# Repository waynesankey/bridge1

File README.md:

This is a PCB design for a UART to WiFi bridge that goes with the bridge1_sw repo software.

The bridge has a Raspberry Pi Pico 2W microcontroller and runs AI generated MicroPython code.

The bridge is used to provide a web browser interface to remotely control a preamp.  The UART
connects to a microcontroller in the preamp that controls the local display, inputection relays,
mute relay, volume control chips, etc.

The bridge is housed in an inexpensive plastic box that need not be visible to the user and
is connected to the preamp by a 4-pin M12 A-coded umbilical cable.  The cable has female ends, while the
bridge and preamp both have 4-pin M12 A-coded male ends.

The signal chain is:

iPhone <-> WiFi <-> BRIDGE1 (Raspberry Pi Pico 2W) <-> UART (4-pin M12 cable) <-> Preamp (Raspberry Pi Pico)

And the iPhone controls and GUI show the state of the Preamp which holds the true state of the
system - so eg. if the volume decoder on the Preamp is used to adjust the volume, that change is
immediately seen on the iPhone GUI.

W. Sankey
2/9/26

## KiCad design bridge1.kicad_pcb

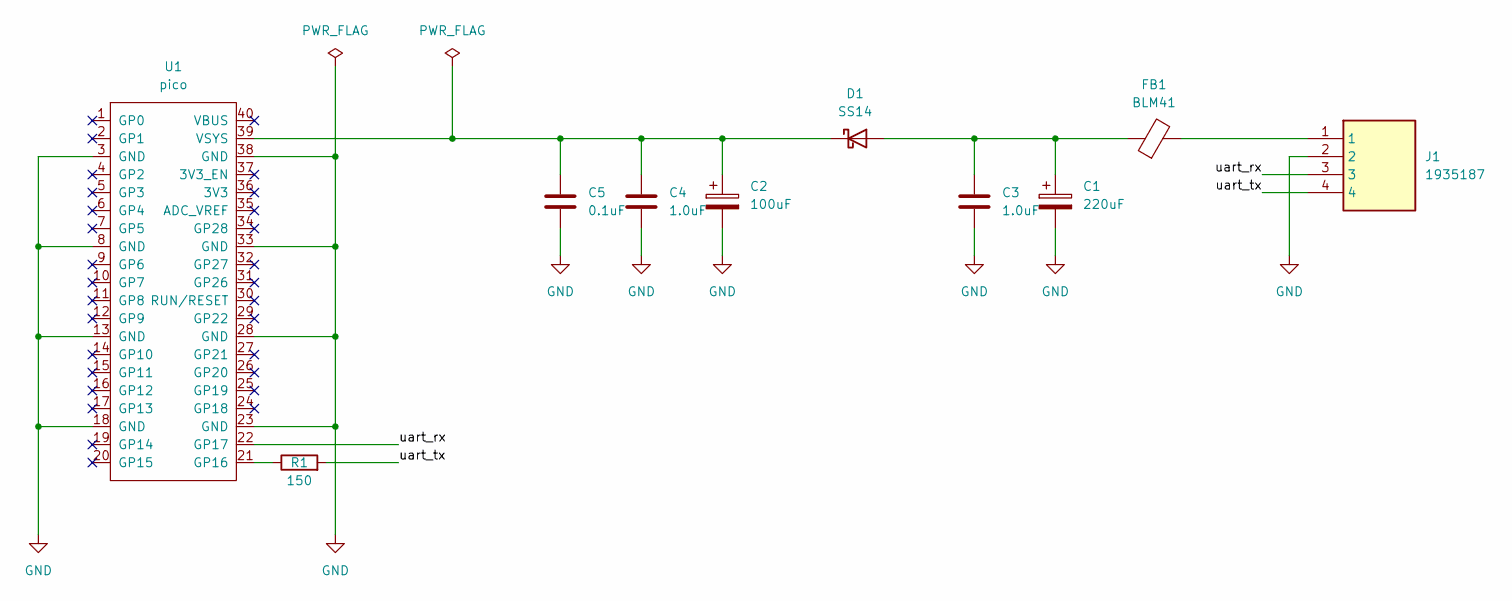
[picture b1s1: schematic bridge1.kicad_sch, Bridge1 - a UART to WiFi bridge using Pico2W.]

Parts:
C1: 220uF; EEE1AA221P
C2: 100uF; 16SVF180M
C3, C4: 1.0uF; C_1206_3216Metric
C5: 0.1uF; C_1206_3216Metric
D1: SS14; D_SMA
FB1: BLM41; L_1806_4516Metric
J1: 1935187; Mouser Part Number 651-1935187
R1: 150; R_0603_1608Metric
U1: pico; RaspberryPi_Pico_Common_Unspecified

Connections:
/uart_rx: J1.3, U1.22 (GP17)
/uart_tx: J1.4, R1.2
GND: C1.2, C2.2, C3.2, C4.2, C5.2, J1.2, U1.3 (GND), U1.8 (GND), U1.13 (GND), U1.18 (GND), U1.23 (GND), U1.28 (GND), U1.33 (GND), U1.38 (GND)
unnamed: C1.1, C3.1, D1.2 (A), FB1.1
unnamed: C2.1, C4.1, C5.1, D1.1 (K), U1.39 (VSYS)
unnamed: FB1.2, J1.1
unnamed: R1.1, U1.21 (GP16)

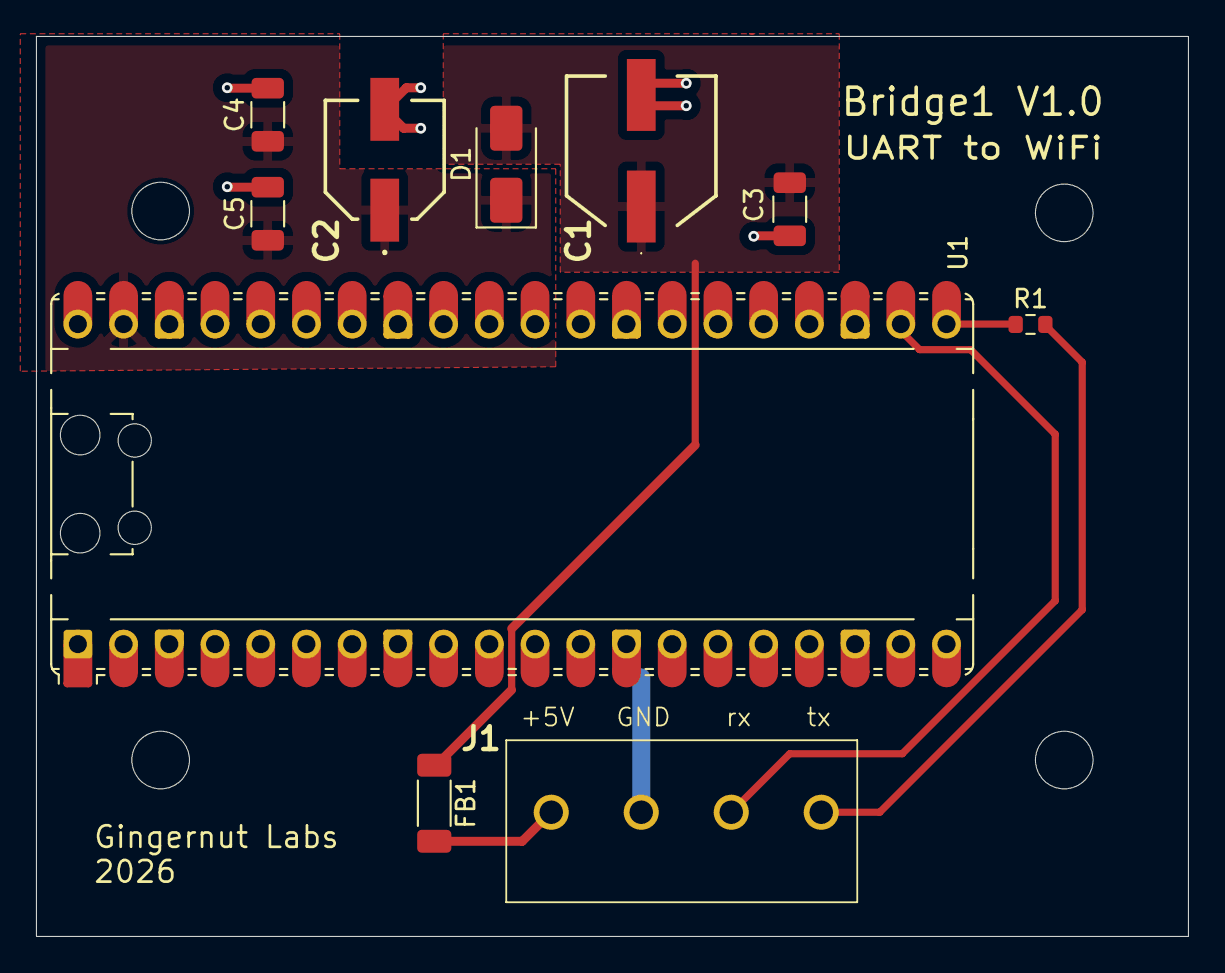
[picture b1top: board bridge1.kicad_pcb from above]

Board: 2 copper layers, 64.0 x 50.0 mm, 10 parts (0 on the bottom side), 7 nets.

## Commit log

2026-02-06 Add KiCad .gitignore
2026-02-06 Initial schematic design for bridge
2026-02-07 Updated schematic and project files with full design
2026-02-07 add fabrication-toolkit-options.json
2026-02-07 Ignore JLCPCB plugin outputs
2026-02-07 Ignore JLCPCB auto-saved files
2026-02-07 Updated schematic to fix duplicated annotations on copied GND symbols, no functional change. ERC passes on this commit.
2026-02-08 Updated schematic and PCB files with JLCPCB parts and PCB design underway
2026-02-08 Ignore JLCPCB plugin workspace
2026-02-08 Updated schematic and PCB files, have full layout now.
2026-02-08 Updated PCB file to remove ground plane under pico 2W for RF transmission
2026-02-08 Updated schematic and PCB files to change R1 to 0603 package, J1 to green screw terminal block.
2026-02-08 Updated PCB file to optimize layout a bit, add silkscreen text.
2026-02-09 Updated PCB file to properly place mounting holes.
2026-02-09 Updated PCB file to widen the UART tracks to 0.4mm from 0.2mm
2026-02-09 added BoM bridge1.csv
2026-02-09 Added README.md
2026-02-09 updated project and pcb files post-ordering V1 PCBs - added 3D models to C1 and C2. No change to design.
